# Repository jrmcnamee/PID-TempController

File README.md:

# PID-TempController
Lab project to control the temperature of water using an Arduino and a PID algorithm

## Proportional-Integral-Derivative Algorithms
A Proportional-Integral-Derivative Algorithm can be used in controllers to minimize the difference betweent the output and the desired state of the system. A PID is a classic closed-loop feedback system, meaning it takes an input and then systematically compares current state to its input over time. The image below shows a simple version of a closed loop system. The PID is simple and easy to implement, making it an attractive choice for many automated processes.

There are many applications for the PID controller, but it's used most often in regulation. For example, the current goal for my PID is to simply regulate water temperature using a probe and heating rod.

### Walking 100 meters; example
So imagine you need to walk forward 100 meters for a sobriety test (**that is one demanding cop!**). Of course, you're sober, but the cop is having a bad night so he demands you walk exactly 100 meters. You only pass if you stop within 0.1 meters of the goal. If you think about it, this is a clever test, because drunk people do not understand control systems! Another rule: **you cannot stop until you're done, reverse, or speed up after slowing down!** This'll come into play in a second.

So, how do you proceed? Well, the cop gives you a watch that tells you your position every second, and you have a brain that sets your velocity with devastating accuracy. Thats easy! Just stop when the watch says 99.9. But wait, theres a caveat: the watch only updates every second. One miss-step near the goal and you fail, and the watch won't update fast enough to  So what you do first is select your **gain**. The gain is very simple: select your gain, multipy it by your distance, and then thats the new velocity you will walk. Since a fast human walking pace is 2.5 meters per second, you select a gain of 0.025, as 100 meters * 0.025 $$s^{-1}$$ is 2.5 m/s. Your distance to time graph will look something like this.

Your position will approach the goal asymptotically until you get within 0.1 meters. The cop is stunned, but daps you up for your incredible math abilities. Thankfully for you, you simple cannot walk fast enough to blow past your target. However, if it *were* possible to select a gain of, say, 1.9, your graph would look like 

So lets talk a little bit more of P, I, and D.
Note that in this example, you technically need that tolerance the cop gave, otherwise you never will really arrive at the destination.

## Proportional Gain, K<sub>p</sub>
Propotional gain was exemplified just before this in the walking example. Its a good way to correct your behavior as you approach the target. However, there are many ways for this to go wrong. Imagine that instead of walking, you're climbing, and gain * error sets the force you climb with. Obviously, you will stop dead in your tracks if the force you move up with ever equals the force of gravity, or your weight. This is called steady state error, and it will result in you never making it to the target. Also, think about it for a heating apparatus: if a certain amount of applied voltage corresponds to a certain amount of heat loss per minute and the rate of heat emmission by the heated system ever becomes equal, you'll be screwed. Whoops!

Proportional gain cannot account for steady state error, or mitigate oscillations. It's the principal component of gain, and extremely influential in the PID. Play around with it using my python code for a basic PID, it'll really shock you how much it governs the system! Try to see if you can get it to reach a steady state (hint: add a term of pushback against proportional gain!)

## Integral Gain, K<sub>i</sub>

Integral gain stockpiles error and provides a proportional signal to the integral over the time. Seems simple, right? This is a great solution to the steady state error connundrum, as persistant, constant error ultimately results in the increase of the provided signal, preventing stability anywhere other than the target. An appropriate integral gain coefficient will make a clean descent/ascent to the target, but one too large will result in "integral windup" which is this fun oscillating value over to the right. The integral and proportional terms should not exist without one another, as they cover eachothers' bases very well.

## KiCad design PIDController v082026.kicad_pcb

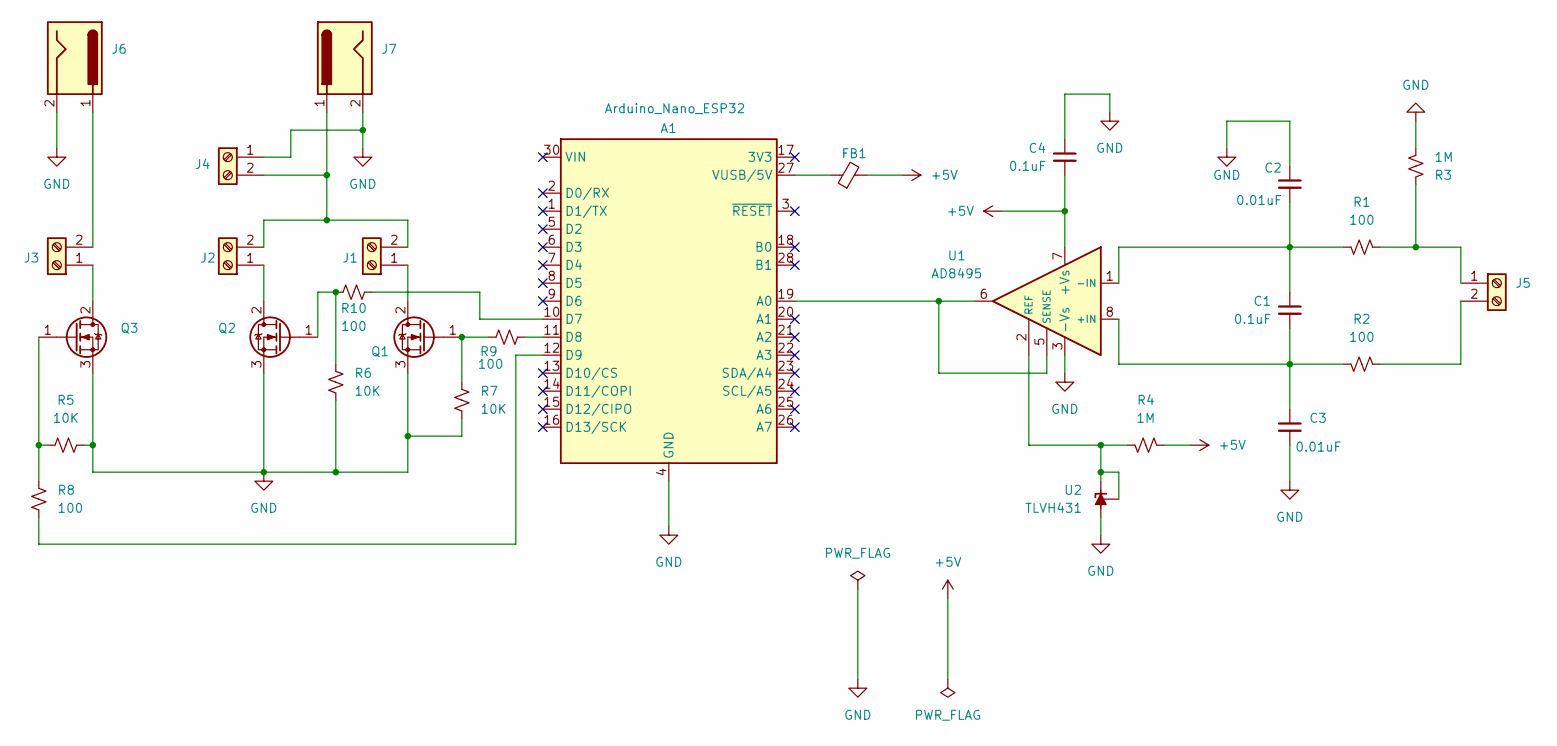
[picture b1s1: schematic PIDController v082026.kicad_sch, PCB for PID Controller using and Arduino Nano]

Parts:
A1: Arduino_Nano_ESP32; Arduino_Nano
C1, C4: 0.1uF; C_0603_1608Metric
C2, C3: 0.01uF; C_0603_1608Metric
FB1: FerriteBead_Small; L_0603_1608Metric
J1, J2, J3, J4, J5: Screw_Terminal_01x02; TerminalBlock_Phoenix_MKDS-1,5-2_1x02_P5.00mm_Horizontal
J6, J7: Jack-DC; BarrelJack_CUI_PJ-063AH_Horizontal
Q1, Q2, Q3: IRLZ44N; TO-220-3_Vertical
R1, R2, R8, R9, R10: 100; R_0603_1608Metric
R3, R4: 1M; R_0603_1608Metric
R5, R6, R7: 10K; R_0603_1608Metric
U1: AD8495; MSOP-8_3x3mm_P0.65mm
U2: TLVH431; SOT-23

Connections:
+5V: C4.2, FB1.2, R4.1, U1.7 (+Vs)
GND: A1.4 (GND), A1.29 (GND), C2.1, C3.2, C4.1, J4.1, J6.2, J7.2, Q1.3 (S), Q2.3 (S), Q3.3 (S), R3.2, R5.1, R6.2, R7.2, U1.3 (-Vs), U2.3 (A)
unnamed: A1.19 (A0), U1.5 (SENSE), U1.6
unnamed: A1.10 (D7), R10.2
unnamed: A1.11 (D8), R9.2
unnamed: A1.12 (D9), R8.2
unnamed: A1.27 (VUSB/5V), FB1.1
unnamed: J1.1, Q1.2 (D)
unnamed: J1.2, J2.2, J4.2, J7.1
unnamed: J2.1, Q2.2 (D)
unnamed: J3.1, Q3.2 (D)
unnamed: J3.2, J6.1
unnamed: J5.1, R1.1, R3.1
unnamed: J5.2, R2.1
unnamed: Q1.1 (G), R7.1, R9.1
unnamed: Q2.1 (G), R6.1, R10.1
unnamed: Q3.1 (G), R5.2, R8.1
unnamed: C1.2, C3.1, R2.2, U1.8 (+IN)
unnamed: C1.1, C2.2, R1.2, U1.1 (-IN)
unnamed: R4.2, U1.2 (REF), U2.1 (K), U2.2 (REF)

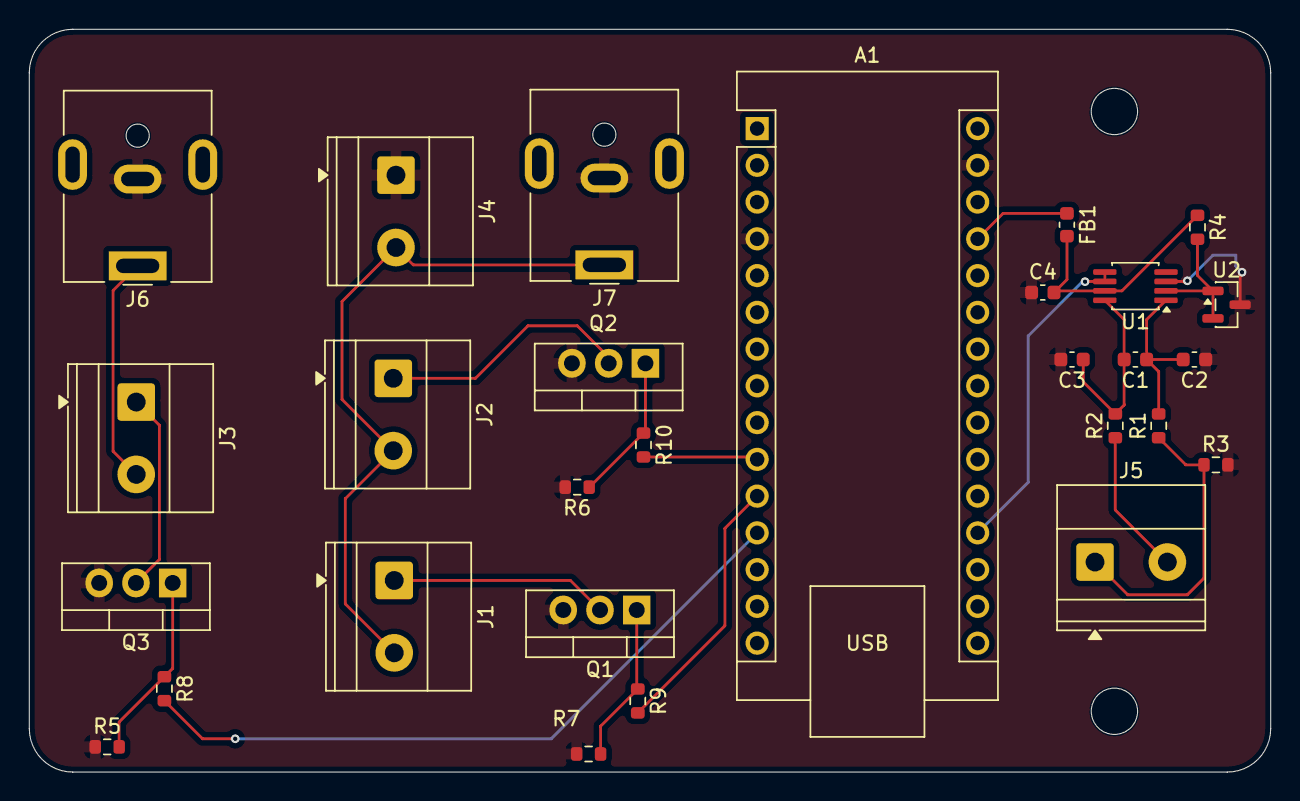
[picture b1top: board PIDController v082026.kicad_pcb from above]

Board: 2 copper layers, 85.8 x 51.3 mm, 28 parts (0 on the bottom side), 20 nets.

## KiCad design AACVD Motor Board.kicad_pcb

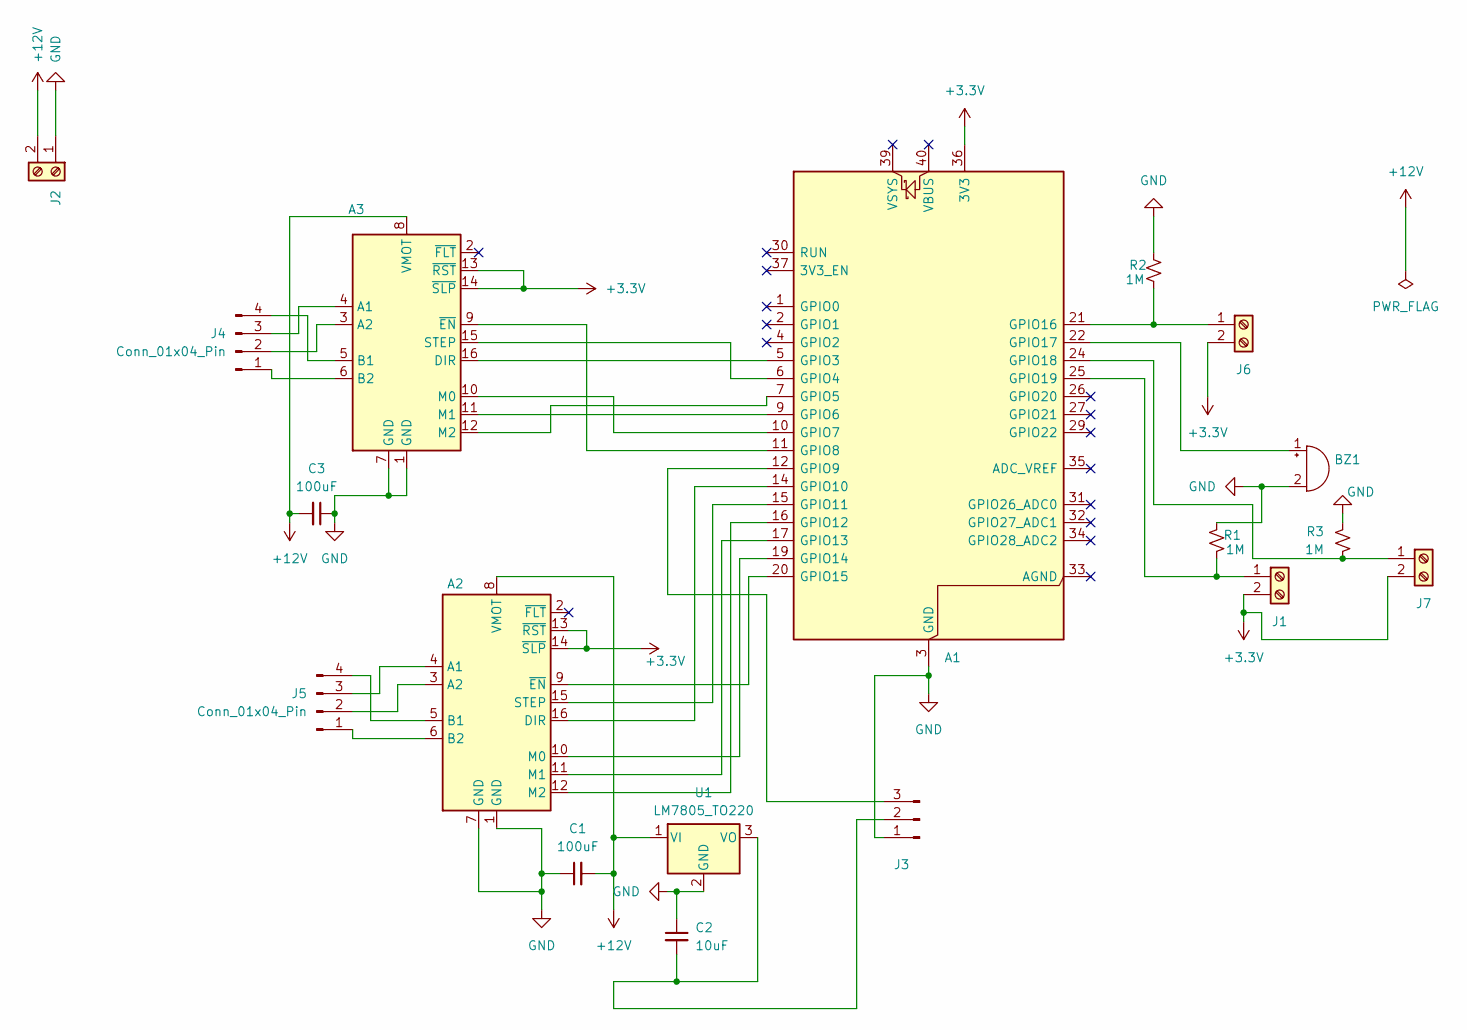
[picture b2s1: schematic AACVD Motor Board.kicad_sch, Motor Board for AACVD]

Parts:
A1: RaspberryPi_Pico; RaspberryPi_Pico_Common_Unspecified
A2, A3: Pololu_Breakout_DRV8825; Pololu_Breakout-16_15.2x20.3mm
BZ1: Buzzer; Buzzer_12x9.5RM7.6
C1, C3: 100uF; C_0603_1608Metric
C2: 10uF; C_0603_1608Metric
J1, J2, J6, J7: Screw_Terminal_01x02; TerminalBlock_Phoenix_MKDS-1,5-2_1x02_P5.00mm_Horizontal
J3: Conn_01x03_Pin; PinHeader_1x03_P2.54mm_Vertical
J4, J5: Conn_01x04_Pin; PinHeader_1x04_P2.00mm_Vertical
R1, R2, R3: 1M; R_0603_1608Metric
U1: LM7805_TO220; TO-220-3_Vertical

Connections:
+3.3V: A1.36 (3V3), A2.13 (~RST), A2.14 (~SLP), A3.13 (~RST), A3.14 (~SLP), J1.2, J6.2, J7.2
+12V: A2.8 (VMOT), A3.8 (VMOT), C1.2, C3.2, J2.2, U1.1 (VI)
GND: A1.3 (GND), A1.8 (GND), A1.13 (GND), A1.18 (GND), A1.23 (GND), A1.28 (GND), A1.38 (GND), A2.1 (GND), A2.7 (GND), A3.1 (GND), A3.7 (GND), BZ1.2 (-), C1.1, C2.1, C3.1, J2.1, J3.1, R1.1, R2.1, R3.1, U1.2 (GND)
unnamed: A1.5 (GPIO3), A3.16 (DIR)
unnamed: A1.6 (GPIO4), A3.15 (STEP)
unnamed: A1.7 (GPIO5), A3.12 (M2)
unnamed: A1.9 (GPIO6), A3.11 (M1)
unnamed: A1.10 (GPIO7), A3.10 (M0)
unnamed: A1.11 (GPIO8), A3.9 (~EN)
unnamed: A1.12 (GPIO9), J3.3
unnamed: A1.14 (GPIO10), A2.16 (DIR)
unnamed: A1.15 (GPIO11), A2.15 (STEP)
unnamed: A1.16 (GPIO12), A2.12 (M2)
unnamed: A1.17 (GPIO13), A2.11 (M1)
unnamed: A1.19 (GPIO14), A2.10 (M0)
unnamed: A1.20 (GPIO15), A2.9 (~EN)
unnamed: A1.21 (GPIO16), J6.1, R2.2
unnamed: A1.22 (GPIO17), BZ1.1 (+)
unnamed: A1.24 (GPIO18), J7.1, R3.2
unnamed: A1.25 (GPIO19), J1.1, R1.2
unnamed: A2.4 (A1), J5.3
unnamed: A2.3 (A2), J5.2
unnamed: A2.5 (B1), J5.4
unnamed: A2.6 (B2), J5.1
unnamed: A3.4 (A1), J4.3
unnamed: A3.3 (A2), J4.2
unnamed: A3.5 (B1), J4.4
unnamed: A3.6 (B2), J4.1
unnamed: C2.2, J3.2, U1.3 (VO)

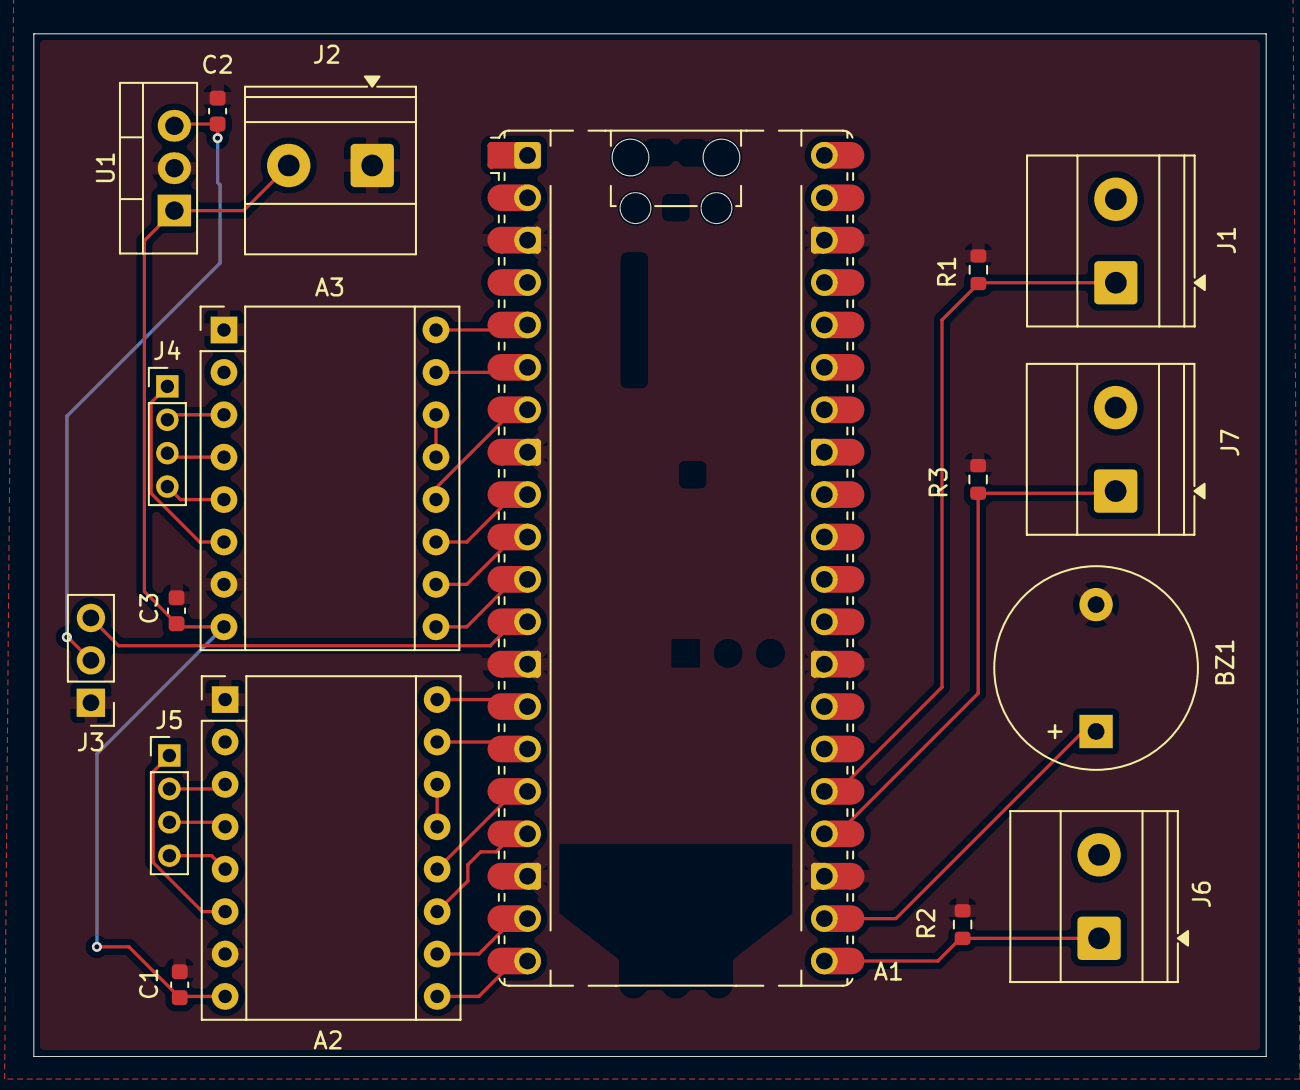
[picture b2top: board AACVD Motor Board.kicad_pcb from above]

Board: 2 copper layers, 73.8 x 61.3 mm, 18 parts (0 on the bottom side), 29 nets.
